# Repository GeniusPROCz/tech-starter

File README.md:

# tech-starter

Autor / Author: Jan Suttner (alias GeniusPROCz)
Rok / Year: © 2025
Verze licence / License Version: 1.0 — Custom Non-Commercial License

🛡️ Právní upozornění / Legal Notice

Tento projekt, včetně všech svých současných i budoucích částí (software, firmware, schémata, návrhy PCB, 3D modely, dokumentace, texty a obrázky), je chráněn autorským právem podle zákona č. 121/2000 Sb. (CZ) a mezinárodních úmluv (Berne Convention).
Použitím, kopírováním, úpravou nebo sdílením tohoto díla souhlasíš s níže uvedenými licenčními podmínkami.
Pokud s nimi nesouhlasíš, nemáš právo projekt nebo jeho části jakkoli používat, upravovat ani šířit.

📘 Tento projekt podléhá licenčním podmínkám uvedeným v sekci „📜 Licenční podmínky / License & Usage Terms“ níže.

📜 Licenční podmínky / License & Usage Terms

Autor / Author: Jan Suttner (GeniusPROCz)
Projekt / Project: tech-starter
Licence / License: Custom Non-Commercial License
Komerční použití / Commercial Use: Pouze po písemné dohodě s autorem / Only with author’s written consent

🇨🇿 Česká verze (právně závazná v ČR)

Autor uděluje uživatelům následující oprávnění:

✅ Povolené použití

Používat, upravovat a sdílet tento projekt pro osobní, vzdělávací a nekomerční účely.

Prezentovat nebo forkovat projekt za předpokladu zachování uvedení autora:

© 2025 Jan Suttner (GeniusPROCz) — originální projekt: 
🚫 Zakázané použití

Jakékoli komerční využití (prodej, výroba, reklama, monetizace, placené služby atd.) bez písemného souhlasu autora.

Přivlastnění si autorství, úprava či odstranění označení původního autora.

Šíření bez tohoto licenčního textu nebo bez odkazu na původní repozitář.

⚙️ Shrnutí práv
Právo	Stav
Osobní / vzdělávací použití	✅ Povoleno
Úpravy a sdílení (s uvedením autora)	✅ Povoleno
Komerční použití	⚠️ Pouze po písemné dohodě s autorem
Přivlastnění / šíření bez zdroje	❌ Zakázáno
⚠️ Prohlášení

Projekt je poskytován „tak, jak je“ (as is) bez jakékoli záruky. Autor nenese odpovědnost za škody vzniklé použitím nebo modifikací materiálů.

🇬🇧 English Version (internationally equivalent)

The author grants the following permissions:

✅ Allowed

Use, modify and share this project for personal, educational and non-commercial purposes.

Publicly present or fork this repository with proper credit to the author:

© 2025 Jan Suttner (GeniusPROCz) — original project: 
🚫 Prohibited

Any commercial use (sales, production, advertising, monetization, paid services, etc.) without prior written consent from the author.

Removing or altering author attribution.

Redistributing this work without this license text or a link to the original repository.

⚙️ Rights Summary
Right	Status
Personal / educational use	✅ Allowed
Modification & redistribution (with credit)	✅ Allowed
Commercial use	⚠️ Only with written permission
Misattribution / uncredited redistribution	❌ Forbidden
⚠️ Disclaimer

This project is provided “as is”, without any warranty of any kind. The author shall not be liable for any damages arising from use or modification.

✅ Použitím tohoto repozitáře výslovně souhlasíš s výše uvedenými podmínkami.
Jakékoli komerční použití bez souhlasu autora může být považováno za porušení autorských práv (§ 12 a násl. zákona č. 121/2000 Sb.).

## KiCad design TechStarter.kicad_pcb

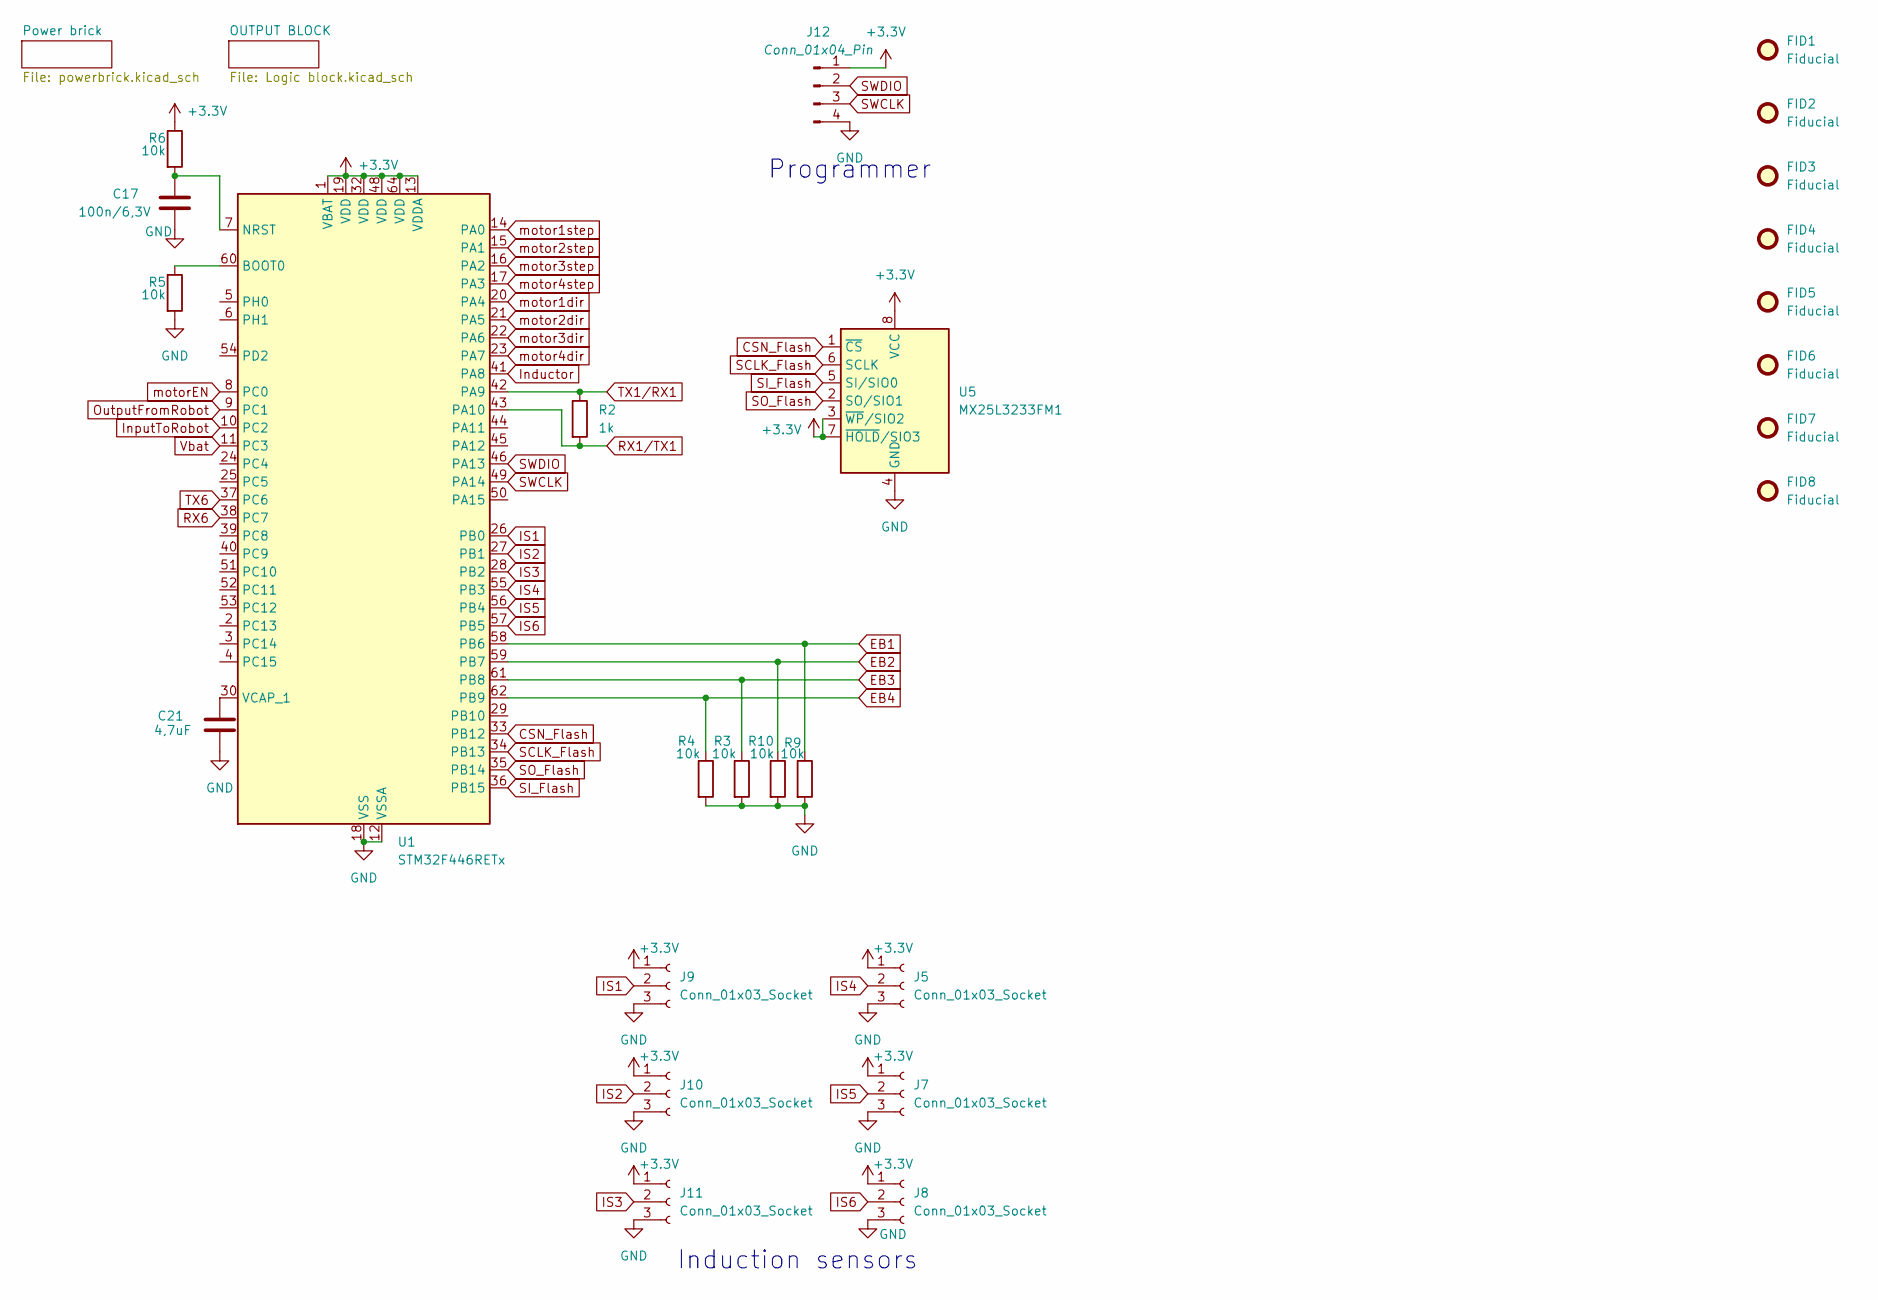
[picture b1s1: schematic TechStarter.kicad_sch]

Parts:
C17: 100n/6,3V; C_0603_1608Metric
C21: 4,7uF; C_Elec_10x10.2
FID1, FID2, FID3, FID4, FID5, FID6, FID7, FID8: Fiducial; Fiducial_0.75mm_Mask1.5mm
J5, J7, J8, J9, J10, J11: Conn_01x03_Socket; JST_XH_S3B-XH-A_1x03_P2.50mm_Horizontal
J12: Conn_01x04_Pin; PinSocket_1x04_P2.54mm_Vertical_SMD_Pin1Left
R2: 1k; R_0603_1608Metric
R3, R4, R5, R6, R9, R10: 10k; R_0603_1608Metric
U1: STM32F446RETx; LQFP-64_10x10mm_P0.5mm
U5: MX25L3233FM1; JEITA_SOIC-8_3.9x4.9mm_P1.27mm

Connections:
+3.3V: J5.1, J7.1, J8.1, J9.1, J10.1, J11.1, J12.1, R6.1, U1.1 (VBAT), U1.13 (VDDA), U1.19 (VDD), U1.32 (VDD), U1.48 (VDD), U1.64 (VDD), U5.3 (~WP/SIO2), U5.7 (~HOLD/SIO3), U5.8 (VCC); also elsewhere on the board
CSN_Flash: U1.33 (PB12), U5.1 (~CS)
EB1: R9.1, U1.58 (PB6); also elsewhere on the board
EB2: R10.1, U1.59 (PB7); also elsewhere on the board
EB3: R3.1, U1.61 (PB8); also elsewhere on the board
EB4: R4.1, U1.62 (PB9); also elsewhere on the board
GND: C17.2, C21.2, J5.3, J7.3, J8.3, J9.3, J10.3, J11.3, J12.4, R3.2, R4.2, R5.2, R9.2, R10.2, U1.12 (VSSA), U1.18 (VSS), U1.31 (VSS), U1.47 (VSS), U1.63 (VSS), U5.4 (GND); also elsewhere on the board
IS1: J9.2, U1.26 (PB0)
IS2: J10.2, U1.27 (PB1)
IS3: J11.2, U1.28 (PB2)
IS4: J5.2, U1.55 (PB3)
IS5: J7.2, U1.56 (PB4)
IS6: J8.2, U1.57 (PB5)
Inductor: U1.41 (PA8); also elsewhere on the board
InputToRobot: U1.10 (PC2); also elsewhere on the board
unnamed: R5.1, U1.60 (BOOT0)
unnamed: C17.1, R6.2, U1.7 (NRST)
unnamed: C21.1, U1.30 (VCAP_1)
OutputFromRobot: U1.9 (PC1); also elsewhere on the board
RX1/TX1: R2.2, U1.43 (PA10); also elsewhere on the board
RX6: U1.38 (PC7); also elsewhere on the board
SCLK_Flash: U1.34 (PB13), U5.6 (SCLK)
SI_Flash: U1.36 (PB15), U5.5 (SI/SIO0)
SO_Flash: U1.35 (PB14), U5.2 (SO/SIO1)
SWCLK: J12.3, U1.49 (PA14)
SWDIO: J12.2, U1.46 (PA13)
TX1/RX1: R2.1, U1.42 (PA9)
TX6: U1.37 (PC6); also elsewhere on the board
Vbat: U1.11 (PC3)
motor1dir: U1.20 (PA4); also elsewhere on the board
motor1step: U1.14 (PA0); also elsewhere on the board
motor2dir: U1.21 (PA5); also elsewhere on the board
motor2step: U1.15 (PA1); also elsewhere on the board
motor3dir: U1.22 (PA6); also elsewhere on the board
motor3step: U1.16 (PA2); also elsewhere on the board
motor4dir: U1.23 (PA7); also elsewhere on the board
motor4step: U1.17 (PA3); also elsewhere on the board
motorEN: U1.8 (PC0); also elsewhere on the board

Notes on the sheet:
Programmer
Induction sensors

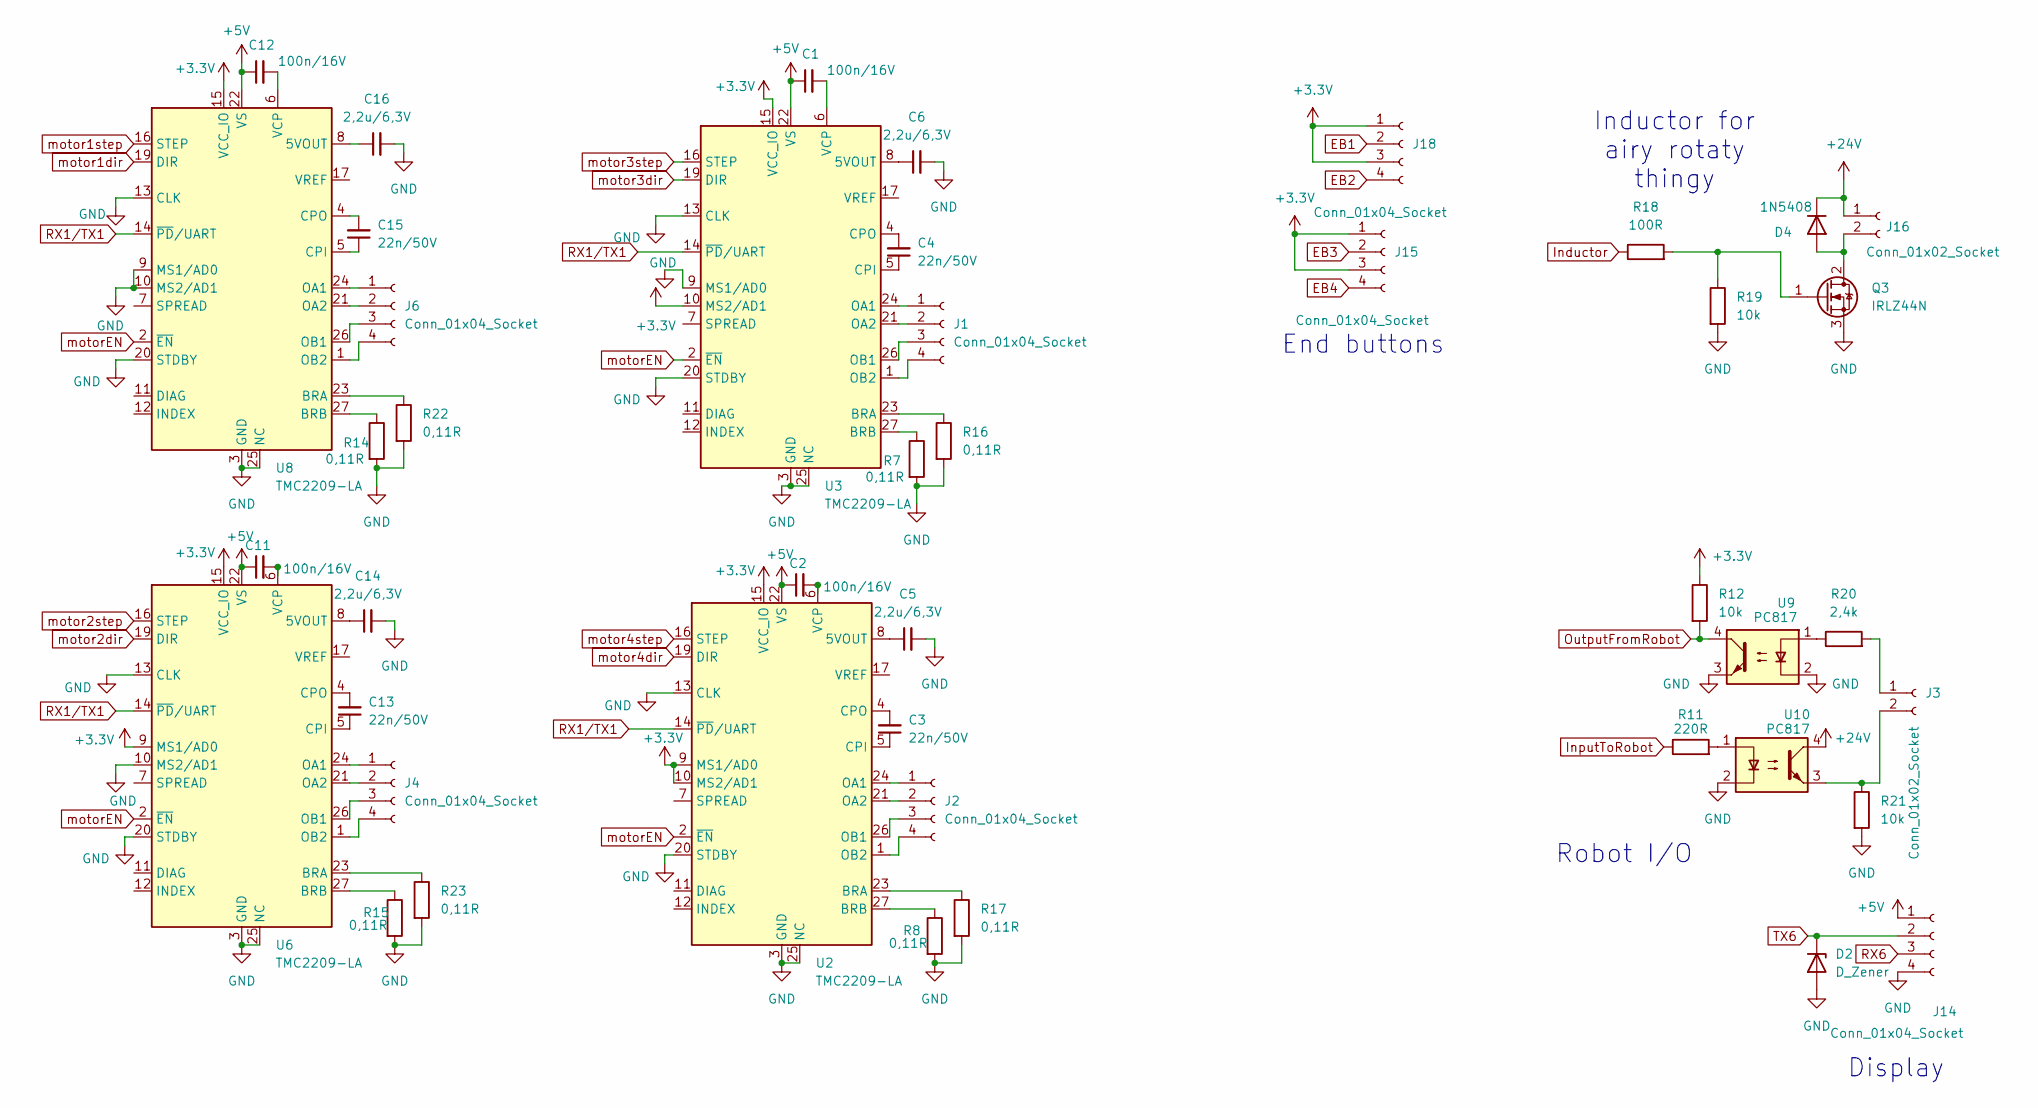
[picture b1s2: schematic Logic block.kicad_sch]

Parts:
C1, C2, C11, C12: 100n/16V; C_0603_1608Metric
C3, C4, C13, C15: 22n/50V; C_0603_1608Metric
C5, C6, C14, C16: 2,2u/6,3V; C_0603_1608Metric
D2: D_Zener; D_MiniMELF
D4: 1N5408; D_DO-201AD_P15.24mm_Horizontal
J1, J2, J4, J6: Conn_01x04_Socket; PhoenixContact_MC_1,5_4-GF-3.81_1x04_P3.81mm_Horizontal_Thr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
J3: Conn_01x02_Socket; JST_XH_S2B-XH-A_1x02_P2.50mm_Horizontal
J14: Conn_01x04_Socket; JST_XH_B4B-XH-A_1x04_P2.50mm_Vertical
J15, J18: Conn_01x04_Socket; JST_XH_S4B-XH-A_1x04_P2.50mm_Horizontal
J16: Conn_01x02_Socket; PhoenixContact_MC_1,5_2-G-3.81_1x02_P3.81mm_Horizontal
Q3: IRLZ44N; TO-220-3_Vertical
R7, R8, R14, R15, R16, R17, R22, R23: 0,11R; R_1206_3216Metric
R11: 220R; R_0603_1608Metric
R12, R19, R21: 10k; R_0603_1608Metric
R18: 100R; R_0603_1608Metric
R20: 2,4k; R_0603_1608Metric
U2, U3, U6, U8: TMC2209-LA; VQFN-28-1EP_5x5mm_P0.5mm_EP3.7x3.7mm_ThermalVias
U9, U10: PC817; DIP-4_W7.62mm

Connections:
+3.3V: J15.1, J15.3, J18.1, J18.3, R12.1, U2.9 (MS1/AD0), U2.10 (MS2/AD1), U2.15 (VCC_IO), U3.10 (MS2/AD1), U3.15 (VCC_IO), U6.9 (MS1/AD0), U6.15 (VCC_IO), U8.15 (VCC_IO); also elsewhere on the board
+5V: C1.1, C2.1, C11.1, C12.1, J14.1, U2.22 (VS), U2.28 (VS), U3.22 (VS), U3.28 (VS), U6.22 (VS), U6.28 (VS), U8.22 (VS), U8.28 (VS); also elsewhere on the board
+24V: D4.1 (K), J16.1, U10.4; also elsewhere on the board
EB1: J18.2; also elsewhere on the board
EB2: J18.4; also elsewhere on the board
EB3: J15.2; also elsewhere on the board
EB4: J15.4; also elsewhere on the board
GND: C5.2, C6.2, C14.2, C16.2, D2.2 (A), J14.4, Q3.3 (S), R7.2, R8.2, R14.2, R15.2, R16.2, R17.2, R19.2, R21.2, R22.2, R23.2, U2.3 (GND), U2.13 (CLK), U2.18 (GND), U2.20 (STDBY), U2.25 (NC), U2.29 (GND), U3.3 (GND), U3.9 (MS1/AD0), U3.13 (CLK), U3.18 (GND), U3.20 (STDBY), U3.25 (NC), U3.29 (GND), U6.3 (GND), U6.10 (MS2/AD1), U6.13 (CLK), U6.18 (GND), U6.20 (STDBY), U6.25 (NC), U6.29 (GND), U8.3 (GND), U8.9 (MS1/AD0), U8.10 (MS2/AD1), U8.13 (CLK), U8.18 (GND), U8.20 (STDBY), U8.25 (NC), U8.29 (GND), U9.2, U9.3, U10.2; also elsewhere on the board
Inductor: R18.1; also elsewhere on the board
InputToRobot: R11.1; also elsewhere on the board
unnamed: D4.2 (A), J16.2, Q3.2 (D)
unnamed: J1.1, U3.24 (OA1)
unnamed: J1.2, U3.21 (OA2)
unnamed: J1.3, U3.26 (OB1)
unnamed: J1.4, U3.1 (OB2)
unnamed: J2.1, U2.24 (OA1)
unnamed: J2.2, U2.21 (OA2)
unnamed: J2.3, U2.26 (OB1)
unnamed: J2.4, U2.1 (OB2)
unnamed: J3.1, R20.2
unnamed: J3.2, R21.1, U10.3
unnamed: J4.1, U6.24 (OA1)
unnamed: J4.2, U6.21 (OA2)
unnamed: J4.3, U6.26 (OB1)
unnamed: J4.4, U6.1 (OB2)
unnamed: J6.1, U8.24 (OA1)
unnamed: J6.2, U8.21 (OA2)
unnamed: J6.3, U8.26 (OB1)
unnamed: J6.4, U8.1 (OB2)
unnamed: Q3.1 (G), R18.2, R19.1
unnamed: R11.2, U10.1
unnamed: R20.1, U9.1
unnamed: C5.1, U2.8 (5VOUT)
unnamed: R17.1, U2.23 (BRA)
unnamed: R8.1, U2.27 (BRB)
unnamed: C3.1, U2.5 (CPI)
unnamed: C3.2, U2.4 (CPO)
unnamed: C2.2, U2.6 (VCP)
unnamed: C6.1, U3.8 (5VOUT)
unnamed: R16.1, U3.23 (BRA)
unnamed: R7.1, U3.27 (BRB)
unnamed: C4.1, U3.5 (CPI)
unnamed: C4.2, U3.4 (CPO)
unnamed: C1.2, U3.6 (VCP)
unnamed: C14.1, U6.8 (5VOUT)
unnamed: R23.1, U6.23 (BRA)
unnamed: R15.1, U6.27 (BRB)
unnamed: C13.1, U6.5 (CPI)
unnamed: C13.2, U6.4 (CPO)
unnamed: C11.2, U6.6 (VCP)
unnamed: C16.1, U8.8 (5VOUT)
unnamed: R22.1, U8.23 (BRA)
unnamed: R14.1, U8.27 (BRB)
unnamed: C15.1, U8.5 (CPI)
unnamed: C15.2, U8.4 (CPO)
unnamed: C12.2, U8.6 (VCP)
OutputFromRobot: R12.2, U9.4; also elsewhere on the board
RX1/TX1: U2.14 (~PD/UART), U3.14 (~PD/UART), U6.14 (~PD/UART), U8.14 (~PD/UART); also elsewhere on the board
RX6: J14.3; also elsewhere on the board
TX6: D2.1 (K), J14.2; also elsewhere on the board
motor1dir: U8.19 (DIR); also elsewhere on the board
motor1step: U8.16 (STEP); also elsewhere on the board
motor2dir: U6.19 (DIR); also elsewhere on the board
motor2step: U6.16 (STEP); also elsewhere on the board
motor3dir: U3.19 (DIR); also elsewhere on the board
motor3step: U3.16 (STEP); also elsewhere on the board
motor4dir: U2.19 (DIR); also elsewhere on the board
motor4step: U2.16 (STEP); also elsewhere on the board
motorEN: U2.2 (~EN), U3.2 (~EN), U6.2 (~EN), U8.2 (~EN); also elsewhere on the board

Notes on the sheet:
Display
End buttons
Inductor for airy rotaty thingy
Robot I/O

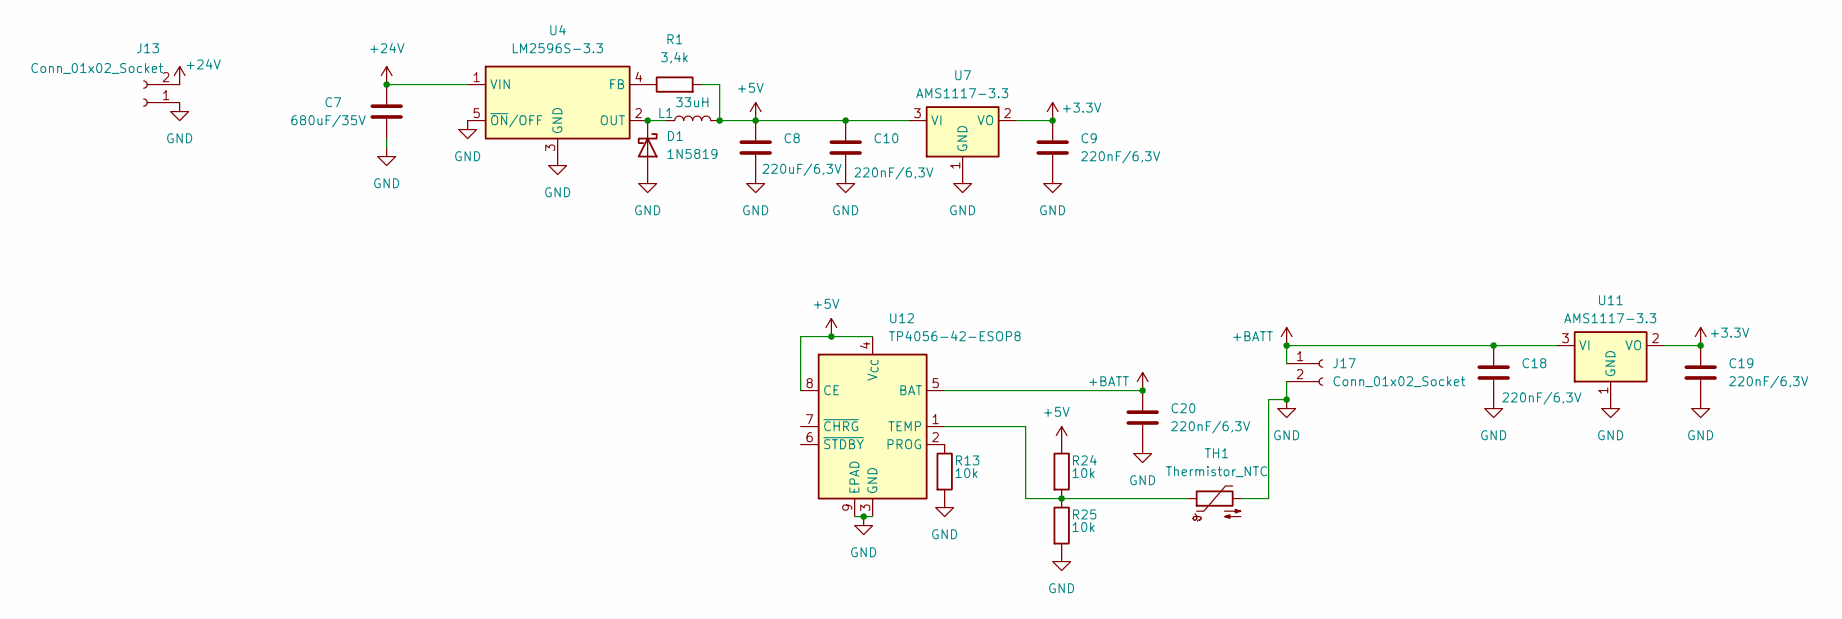
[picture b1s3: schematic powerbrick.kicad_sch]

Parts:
C7: 680uF/35V; C_Elec_10x10.2
C8: 220uF/6,3V; C_Elec_6.3x5.4
C9, C10, C18, C19, C20: 220nF/6,3V; C_0603_1608Metric
D1: 1N5819; D_DO-41_SOD81_P10.16mm_Horizontal
J13: Conn_01x02_Socket; PhoenixContact_MC_1,5_2-GF-3.5_1x02_P3.50mm_Horizontal_Thre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
J17: Conn_01x02_Socket; JST_XH_B2B-XH-A_1x02_P2.50mm_Vertical
L1: 33uH; L_7.3x7.3_H4.5
R1: 3,4k; R_0603_1608Metric
R13, R24, R25: 10k; R_0603_1608Metric
TH1: Thermistor_NTC; R_Axial_DIN0204_L3.6mm_D1.6mm_P2.54mm_Vertical
U4: LM2596S-3.3; TO-263-5_TabPin3
U7, U11: AMS1117-3.3; SOT-223-3_TabPin2
U12: TP4056-42-ESOP8; SOIC-8-1EP_3.9x4.9mm_P1.27mm_EP2.41x3.3mm_ThermalVias_model

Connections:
+3.3V: C9.1, C19.1, U7.2 (VO), U11.2 (VO); also elsewhere on the board
+5V: C8.1, C10.1, L1.2, R1.2, R24.1, U7.3 (VI), U12.4 (V_{CC}), U12.8 (CE); also elsewhere on the board
+24V: C7.1, J13.2, U4.1 (VIN); also elsewhere on the board
+BATT: C18.1, C20.1, J17.1, U11.3 (VI), U12.5 (BAT)
GND: C7.2, C8.2, C9.2, C10.2, C18.2, C19.2, C20.2, D1.2 (A), J13.1, J17.2, R13.2, R25.2, TH1.2, U4.3 (GND), U4.5 (~ON/OFF), U7.1 (GND), U11.1 (GND), U12.3 (GND), U12.9 (EPAD); also elsewhere on the board
unnamed: D1.1 (K), L1.1, U4.2 (OUT)
unnamed: R1.1, U4.4 (FB)
unnamed: R13.1, U12.2 (PROG)
unnamed: R24.2, R25.1, TH1.1, U12.1 (TEMP)

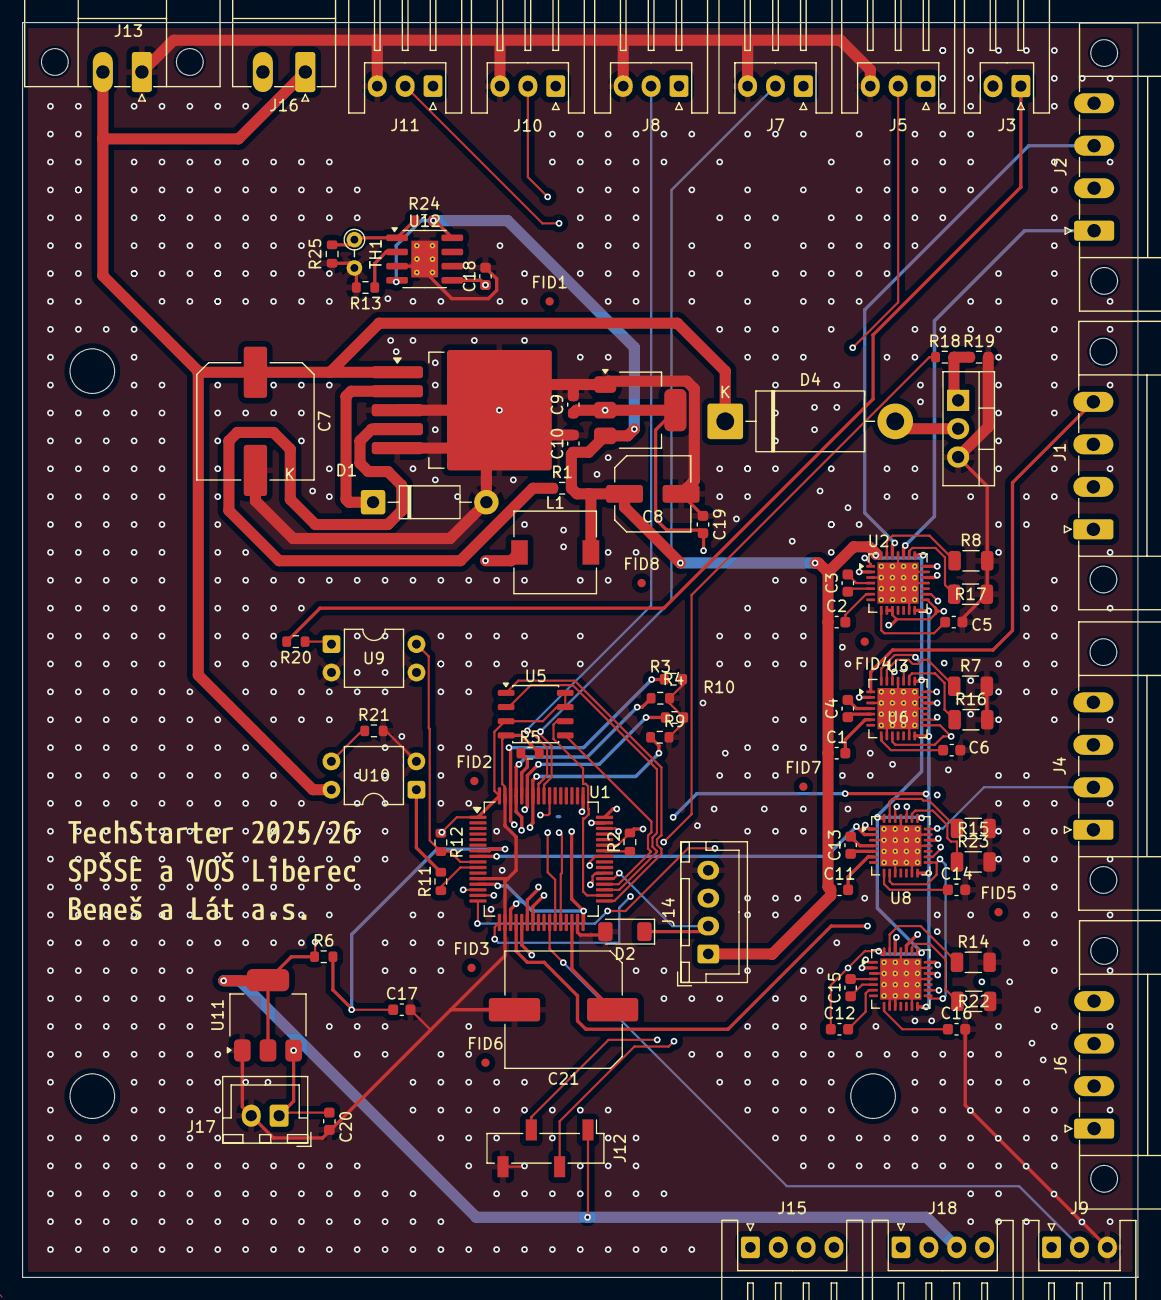
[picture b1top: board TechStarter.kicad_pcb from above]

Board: 4 copper layers, 100.0 x 112.5 mm, 91 parts (0 on the bottom side), 90 nets.

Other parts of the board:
kibuzzard-69317C43: G***; kibuzzard-69317C43

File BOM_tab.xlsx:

Reference | Qty | Value | DNP | Exclude from BOM | Exclude from board | Footprint | Datasheet
C1,C2,C11,C12 | 4 | 100n/16V |  |  |  | Capacitor_SMD:C_0603_1608Metric | ~
C3,C4,C13,C15 | 4 | 22n/50V |  |  |  | Capacitor_SMD:C_0603_1608Metric | ~
C5,C6,C14,C16 | 4 | 2,2u/6,3V |  |  |  | Capacitor_SMD:C_0603_1608Metric | ~
C7,C17 | 2 | 680uF/35V |  |  |  | Capacitor_SMD:C_Elec_10x10.2 | ~
C8 | 1 | 220uF/6,3V |  |  |  | Capacitor_SMD:C_Elec_6.3x5.4 | ~
C9,C10,C18,C19,C20 | 5 | 220nF/6,3V |  |  |  | Capacitor_SMD:C_0603_1608Metric | ~
C21 | 1 | 4,7uF |  |  |  | Capacitor_SMD:C_Elec_10x10.2 | ~
D1 | 1 | 1N5819 |  |  |  | Diode_THT:D_DO-41_SOD81_P10.16mm_Horizontal | http://www.vishay.com/docs/88525/1n5817.pdf
D2 | 1 | D_Zener |  |  |  | Diode_SMD:D_MiniMELF | ~
D4 | 1 | 1N5408 |  |  |  | Diode_THT:D_DO-201AD_P15.24mm_Horizontal | http://www.vishay.com/docs/88516/1n5400.pdf
J1,J2,J4,J6 | 4 | Conn_01x04_Socket |  |  |  | Connector_Phoenix_MC:PhoenixContact_MC_1,5_4-GF-3.81_1x04_P3.81mm_Horizontal_Th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 | ~
J3 | 1 | Conn_01x02_Socket |  |  |  | Connector_JST:JST_XH_S2B-XH-A_1x02_P2.50mm_Horizontal | ~
J5,J7,J8,J9,J10,J11 | 6 | Conn_01x03_Socket |  |  |  | Connector_JST:JST_XH_S3B-XH-A_1x03_P2.50mm_Horizontal | ~
J12 | 1 | Conn_01x04_Pin |  |  |  | Connector_PinSocket_2.54mm:PinSocket_1x04_P2.54mm_Vertical_SMD_Pin1Left | ~
J13 | 1 | Conn_01x02_Socket |  |  |  | Connector_Phoenix_MC:PhoenixContact_MC_1,5_2-GF-3.5_1x02_P3.50mm_Horizontal_Thr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 | ~
J14 | 1 | Conn_01x04_Socket |  |  |  | Connector_JST:JST_XH_B4B-XH-A_1x04_P2.50mm_Vertical | ~
J15,J18 | 2 | Conn_01x04_Socket |  |  |  | Connector_JST:JST_XH_S4B-XH-A_1x04_P2.50mm_Horizontal | ~
J16 | 1 | Conn_01x02_Socket |  |  |  | Connector_Phoenix_MC:PhoenixContact_MC_1,5_2-G-3.81_1x02_P3.81mm_Horizontal | ~
J17 | 1 | Conn_01x02_Socket |  |  |  | Connector_JST:JST_XH_B2B-XH-A_1x02_P2.50mm_Vertical | ~
L1 | 1 | 33uH |  |  |  | Inductor_SMD:L_7.3x7.3_H4.5 | ~
Q3 | 1 | IRLZ44N |  |  |  | Package_TO_SOT_THT:TO-220-3_Vertical | http://www.irf.com/product-info/datasheets/data/irlz44n.pdf
R1 | 1 | 3,4k |  |  |  | Resistor_SMD:R_0603_1608Metric | ~
R2 | 1 | 1k |  |  |  | Resistor_SMD:R_0603_1608Metric | ~
R3,R4,R5,R6,R9,R10,R12,R13,R19,R21,R24,R25 | 12 | 10k |  |  |  | Resistor_SMD:R_0603_1608Metric | ~
R7,R8,R14,R15,R16,R17,R22,R23 | 8 | 0,11R |  |  |  | Resistor_SMD:R_1206_3216Metric | ~
R11 | 1 | 220R |  |  |  | Resistor_SMD:R_0603_1608Metric | ~
R18 | 1 | 100R |  |  |  | Resistor_SMD:R_0603_1608Metric | ~
R20 | 1 | 2,7k |  |  |  | Resistor_SMD:R_0603_1608Metric | ~
TH1 | 1 | Thermistor_NTC |  |  |  | Resistor_THT:R_Axial_DIN0204_L3.6mm_D1.6mm_P2.54mm_Vertical | ~
U1 | 1 | STM32F446RETx |  |  |  | Package_QFP:LQFP-64_10x10mm_P0.5mm | https://www.st.com/resource/en/datasheet/stm32f446re.pdf
U2,U3,U6,U8 | 4 | TMC2209-LA |  |  |  | Package_DFN_QFN:VQFN-28-1EP_5x5mm_P0.5mm_EP3.7x3.7mm_ThermalVias | https://www.analog.com/media/en/technical-documentation/data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
U4 | 1 | LM2596S-3.3 |  |  |  | Package_TO_SOT_SMD:TO-263-5_TabPin3 | http://www.ti.com/lit/ds/symlink/lm2596.pdf
U5 | 1 | MX25L3233FM1 |  |  |  | Package_SO:JEITA_SOIC-8_3.9x4.9mm_P1.27mm | https://www.macronix.com/Lists/Datasheet/Attachments/8377/MX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,%203V,%203…
U7,U11 | 2 | AMS1117-3.3 |  |  |  | Package_TO_SOT_SMD:SOT-223-3_TabPin2 | http://www.advanced-monolithic.com/pdf/ds1117.pdf
U9,U10 | 2 | PC817 |  |  |  | Package_DIP:DIP-4_W7.62mm | http://www.soselectronic.cz/a_info/resource/d/pc817.pdf
U12 | 1 | TP4056-42-ESOP8 |  |  |  | Package_SO:SOIC-8-1EP_3.9x4.9mm_P1.27mm_EP2.41x3.3mm_ThermalVias | https://www.lcsc.com/datasheet/lcsc_datasheet_2410121619_TOP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

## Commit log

2025-11-28 .
    jsem frajer
2025-11-28 posun MCU
    nelíbila se mi jeho poloha
2025-11-28 added start of power brick
    without values
2025-11-29 TMC2209
    Zapojil jsem TMC2209 aby to fungírovalo je tam zapojenej i enable pro nějakej pin na stm32 kdyby jsme je chtěli vypnout + uart může bejt zapojenej tak jak jsem ho zapojil protože pomocí MS1 a MS2 nas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
2025-11-30 MX25L3233FM1 (flash pamět)
    Zapojil jsem flashku, měla by bejt lepčí než ta kterou jsem vybral předtím protože je větší a je NORová takže čtení je rychlejší než u NANDový
2025-12-01 power to ICs
    updated power brick. added CMOS battery
2025-12-01 connectors
    added connectors for induction sensor, display, pneumatic motor and programming. programming and induction sensor connector isn't connected, pneumatic fully done, display connector unkown voltage for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
2025-12-01 .
    finishing connectors
2025-12-01 Values and finishing touches
    I ve seen you put bad values for capacitors in powerbrick and added the value of the feedback resistor, also I redid the inductor circuit because gemini said so and your mosfet was for 20 V not 24 V 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
2025-12-02 .
    označení sekcí
2025-12-02 Robot I/O
    připojil jsem výstup a input z robota přes optočleny a přidal konektor na napájení 24 V
2025-12-03 .
    sortation of things, added variant B
2025-12-03 Board
    started board ...
2025-12-03 .
    .
2025-12-03 RIP
    reason of death
    too much of board for too little time...
2025-12-04 board - done
    still gotta remove the errrors
2025-12-04 BOM
    BOM
2025-12-04 tabulka
    SMRTTTTTTTTTTTTTTTTTTTTTTTTTTTTTTTTTTTTTTTTTTTTTTTTTTTTTTTTTTTTTTTTTTTTTTTTTTTTTTTTTTTTTTTTTTTTTTTTTTTTTTTTTTTTTTTTTTTTTTTTTTTTTTTTTTTTTTTTTTTTTTTTTTTTTTTTTTTTTTTTTTTTTTTTTTTTTTTTTTTTTTTTTTTTTTTTT
2025-12-04 .
    GANG BANG
2025-12-04 Programovací konektor
    Hodil jsem ho normálně ...
2025-12-04 Capacitor + other stuff
    Did a safe of your ass
2025-12-04 .
    JLCCCCCCCCCCCCCCCCCCCCCCCCCCCCCCCCCCCCCCCCCCCCCCCCPCBBBBBBBBBBBBBBBBBBBBBBBBBBBBBBBBBBBBBBBBBB
2025-12-04 .
    NEGR
2025-12-04 ,
    ,
2025-12-04 Resistor Value
    i found that you are an idiot sandwich
2025-12-04 Resistor update
    Nigger
2025-12-04 resist
    zase jsem změnil hodnotu rezistorů :)
2026-01-22 3D models
